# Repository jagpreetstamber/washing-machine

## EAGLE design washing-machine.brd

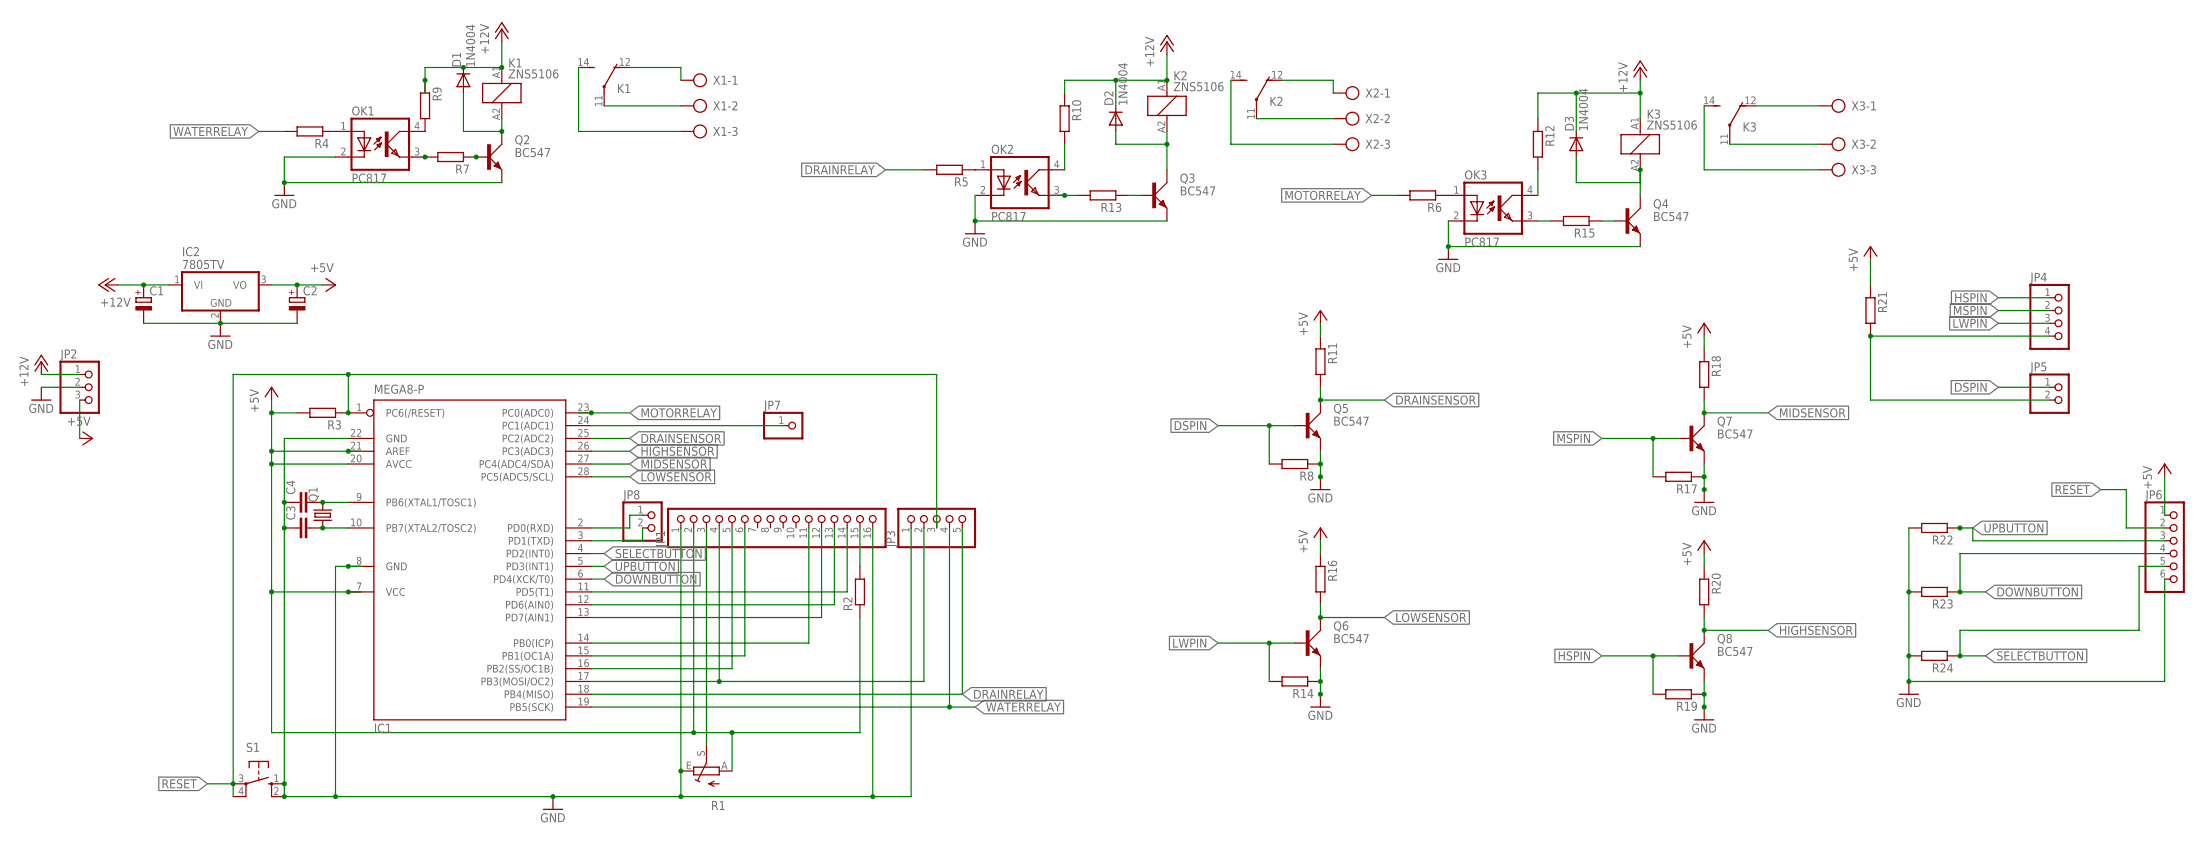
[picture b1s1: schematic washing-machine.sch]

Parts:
C1, C2: CPOL-EUE1.8-4; E1,8-4
C3, C4: C-EU025-024X044; C025-024X044
D1, D2, D3: 1N4004; DO41-10
IC1: MEGA8-P; DIL28-3
IC2: 7805TV; TO220V
JP1: PINHD-1X16; 1X16
JP2: PINHD-1X3; 1X03
JP3: PINHD-1X5; 1X05
JP4: PINHD-1X4; 1X04
JP5, JP8: PINHD-1X2; 1X02
JP6: PINHD-1X6; 1X06
JP7: PINHD-1X1; 1X01
K1, K2, K3: ZNS5106; ZN5
OK1, OK2, OK3: PC817; DIL04
Q1: CRYSTALHC49S; HC49/S
Q2, Q3, Q4, Q5, Q6, Q7, Q8: BC547; SOT54A
R1: TRIM_EU-S63P; S63P
R2, R3, R4, R5, R6, R7, R8, R9, R10, R11, R12, R13, R14, R15, R16, R17, R18, R19, R20, R21, R22, R23, R24: R0204/7; 0204/7
S1: 10-XX; B3F-10XX
X1, X2, X3: AK500/3

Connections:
+5V: C2.+, IC1.7 (VCC), IC1.20 (AVCC), IC1.21 (AREF), IC2.3 (VO), JP1.2, JP2.3, JP6.1, R1.A, R2.1, R3.2, R11.1, R16.1, R18.1, R20.1, R21.1
+12V: C1.+, D1.C, D2.C, D3.C, IC2.1 (VI), JP2.1, K1.A1 (1), K2.A1 (1), K3.A1 (1), R9.1, R10.1, R12.1
DOWNBUTTON: IC1.6 (PD4(XCK/T0)), JP6.4, R23.1
DRAINRELAY: IC1.18 (PB4(MISO)), JP3.5, R5.2
DRAINSENSOR: IC1.25 (PC2(ADC2)), Q5.C, R11.2
DSPIN: JP5.1, Q5.B, R8.2
GND: C1.-, C2.-, C3.1, C4.1, IC1.8 (GND), IC1.22 (GND), IC2.2 (GND), JP1.1, JP1.16, JP2.2, JP3.1, JP6.6, OK1.2 (C), OK2.2 (C), OK3.2 (C), Q2.E, Q3.E, Q4.E, Q5.E, Q6.E, Q7.E, Q8.E, R1.E, R8.1, R14.1, R17.1, R19.1, R22.2, R23.2, R24.2, S1.1 (S), S1.2 (S1)
HIGHSENSOR: IC1.26 (PC3(ADC3)), Q8.C, R20.2
HSPIN: JP4.1, Q8.B, R19.2
LOWSENSOR: IC1.28 (PC5(ADC5/SCL)), Q6.C, R16.2
LWPIN: JP4.3, Q6.B, R14.2
MIDSENSOR: IC1.27 (PC4(ADC4/SDA)), Q7.C, R18.2
MOTORRELAY: IC1.23 (PC0(ADC0)), R6.2
MSPIN: JP4.2, Q7.B, R17.2
unnamed: IC1.13 (PD7(AIN1)), JP1.12
unnamed: IC1.11 (PD5(T1)), JP1.14
unnamed: IC1.12 (PD6(AIN0)), JP1.13
unnamed: IC1.17 (PB3(MOSI/OC2)), JP1.4, JP3.2
unnamed: IC1.16 (PB2(SS/OC1B)), JP1.5
unnamed: IC1.15 (PB1(OC1A)), JP1.6
unnamed: IC1.14 (PB0(ICP)), JP1.11
unnamed: C3.2, IC1.10 (PB7(XTAL2/TOSC2)), Q1.1
unnamed: C4.2, IC1.9 (PB6(XTAL1/TOSC1)), Q1.2
unnamed: OK1.1 (A), R4.1
unnamed: JP1.3, R1.S
unnamed: OK1.3 (EMIT), R7.2
unnamed: Q2.B, R7.1
unnamed: OK2.4 (COL), R10.2
unnamed: D1.A, K1.A2 (2), Q2.C
unnamed: D2.A, K2.A2 (2), Q3.C
unnamed: OK1.4 (COL), R9.2
unnamed: OK2.3 (EMIT), R13.2
unnamed: Q3.B, R13.1
unnamed: OK3.4 (COL), R12.2
unnamed: OK3.3 (EMIT), R15.2
unnamed: Q4.B, R15.1
unnamed: D3.A, K3.A2 (2), Q4.C
unnamed: K3.11, X3.2
unnamed: K2.11, X2.2
unnamed: K1.11, X1.2
unnamed: K1.12 (O), X1.1
unnamed: JP1.15, R2.2
unnamed: K1.14 (S), X1.3
unnamed: K2.12 (O), X2.1
unnamed: IC1.3 (PD1(TXD)), JP8.2
unnamed: OK2.1 (A), R5.1
unnamed: OK3.1 (A), R6.1
unnamed: K2.14 (S), X2.3
unnamed: K3.12 (O), X3.1
unnamed: K3.14 (S), X3.3
unnamed: JP4.4, JP5.2, R21.2
unnamed: IC1.2 (PD0(RXD)), JP8.1
unnamed: IC1.24 (PC1(ADC1)), JP7.1
RESET: IC1.1 (PC6(/RESET)), JP3.3, JP6.2, R3.1, S1.3, S1.4 (P1)
SELECTBUTTON: IC1.4 (PD2(INT0)), JP6.5, R24.1
UPBUTTON: IC1.5 (PD3(INT1)), JP6.3, R22.1
WATERRELAY: IC1.19 (PB5(SCK)), JP3.4, R4.2

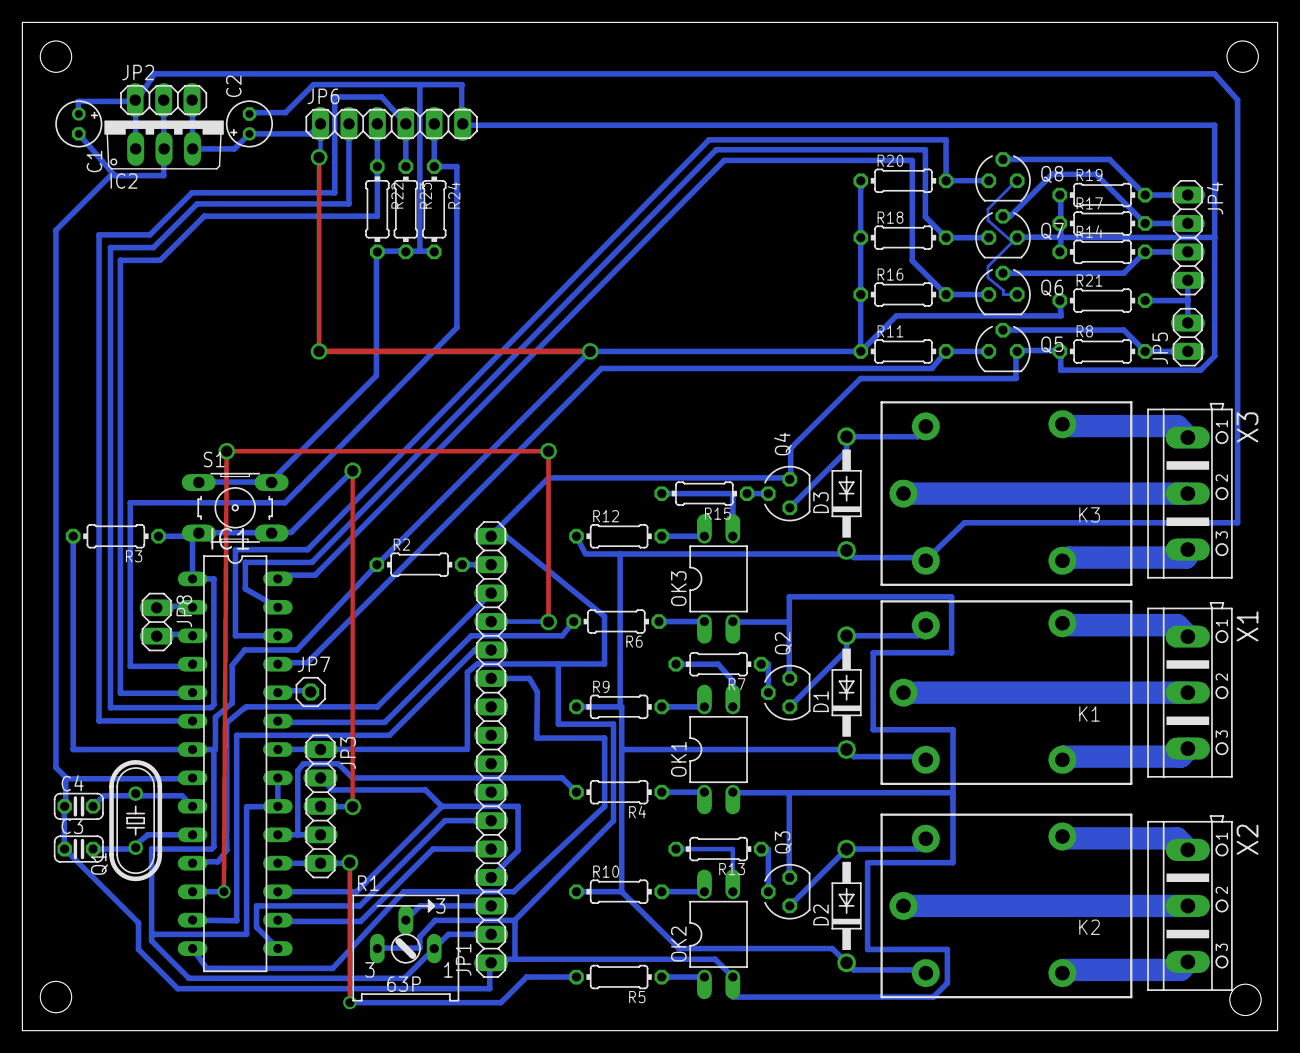
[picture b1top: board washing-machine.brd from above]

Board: 2 copper layers, 112.1 x 90.1 mm, 59 parts (0 on the bottom side), 57 nets.

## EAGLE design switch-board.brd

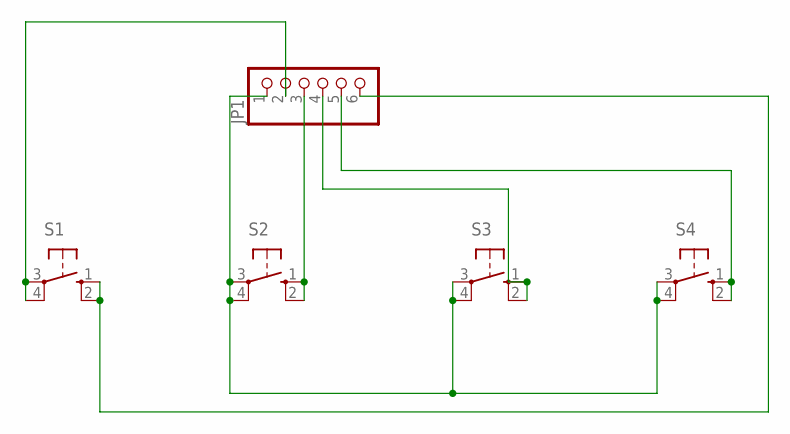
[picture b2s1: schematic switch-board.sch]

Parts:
JP1: PINHD-1X6; 1X06
S1, S2, S3, S4: 10-XX; B3F-10XX

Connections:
unnamed: JP1.1, S2.3, S2.4 (P1), S3.3, S3.4 (P1), S4.3, S4.4 (P1)
unnamed: JP1.3, S2.1 (S), S2.2 (S1)
unnamed: JP1.4, S3.1 (S), S3.2 (S1)
unnamed: JP1.5, S4.1 (S), S4.2 (S1)
unnamed: JP1.6, S1.1 (S), S1.2 (S1)
unnamed: JP1.2, S1.3, S1.4 (P1)

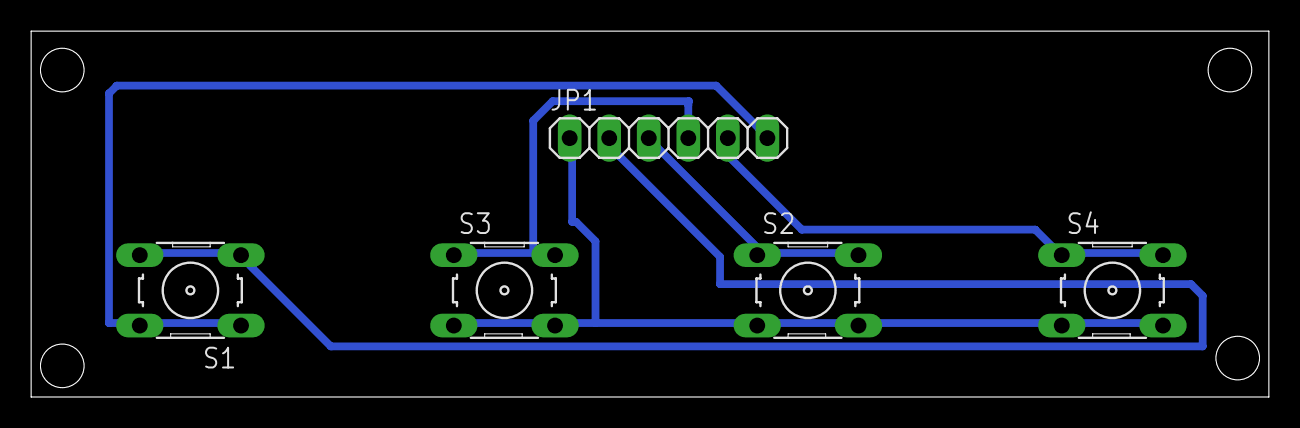
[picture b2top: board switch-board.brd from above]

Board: 2 copper layers, 79.5 x 23.5 mm, 5 parts (0 on the bottom side), 6 nets.

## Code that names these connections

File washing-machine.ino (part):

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
  digitalWrite(waterInletPin, HIGH);
  while (!waterLevelReached) {
    int lowSensor = digitalRead(lowSensorPin);
    int midSensor = digitalRead(midSensorPin);
    int highSensor = digitalRead(highSensorPin);

    if ((selectedWaterLevel == ZERO && lowSensor == LOW) ||
        (selectedWaterLevel == ONE && lowSensor == LOW && midSensor == LOW) ||
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
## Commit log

2016-10-05 Basic flow added
2016-10-05 Center align the text
2016-10-05 Show options with repect to wash mode
2016-10-05 Change default rinse time to 3 min
2016-10-06 Change the ports for the LCD
2016-10-08 Add water drainage and fill up logic
2016-10-08 Add wash and rinse cycle logic
2016-10-08 Change if else if by switch case and reformat code
2016-10-08 Fix the cross initialization errors
2016-10-08 Consider reading from all the sensors for checking if water has drained
2016-10-11 Schematic and board layout added
2016-10-11 Mounting holes added
2016-10-11 Via fixed
2016-10-11 Reroute few wires
2016-10-16 Minor modifications in the layout
2016-10-19 Change layout to increase ground plane
2016-10-29 Remove ground plane to ease of circuit printing
